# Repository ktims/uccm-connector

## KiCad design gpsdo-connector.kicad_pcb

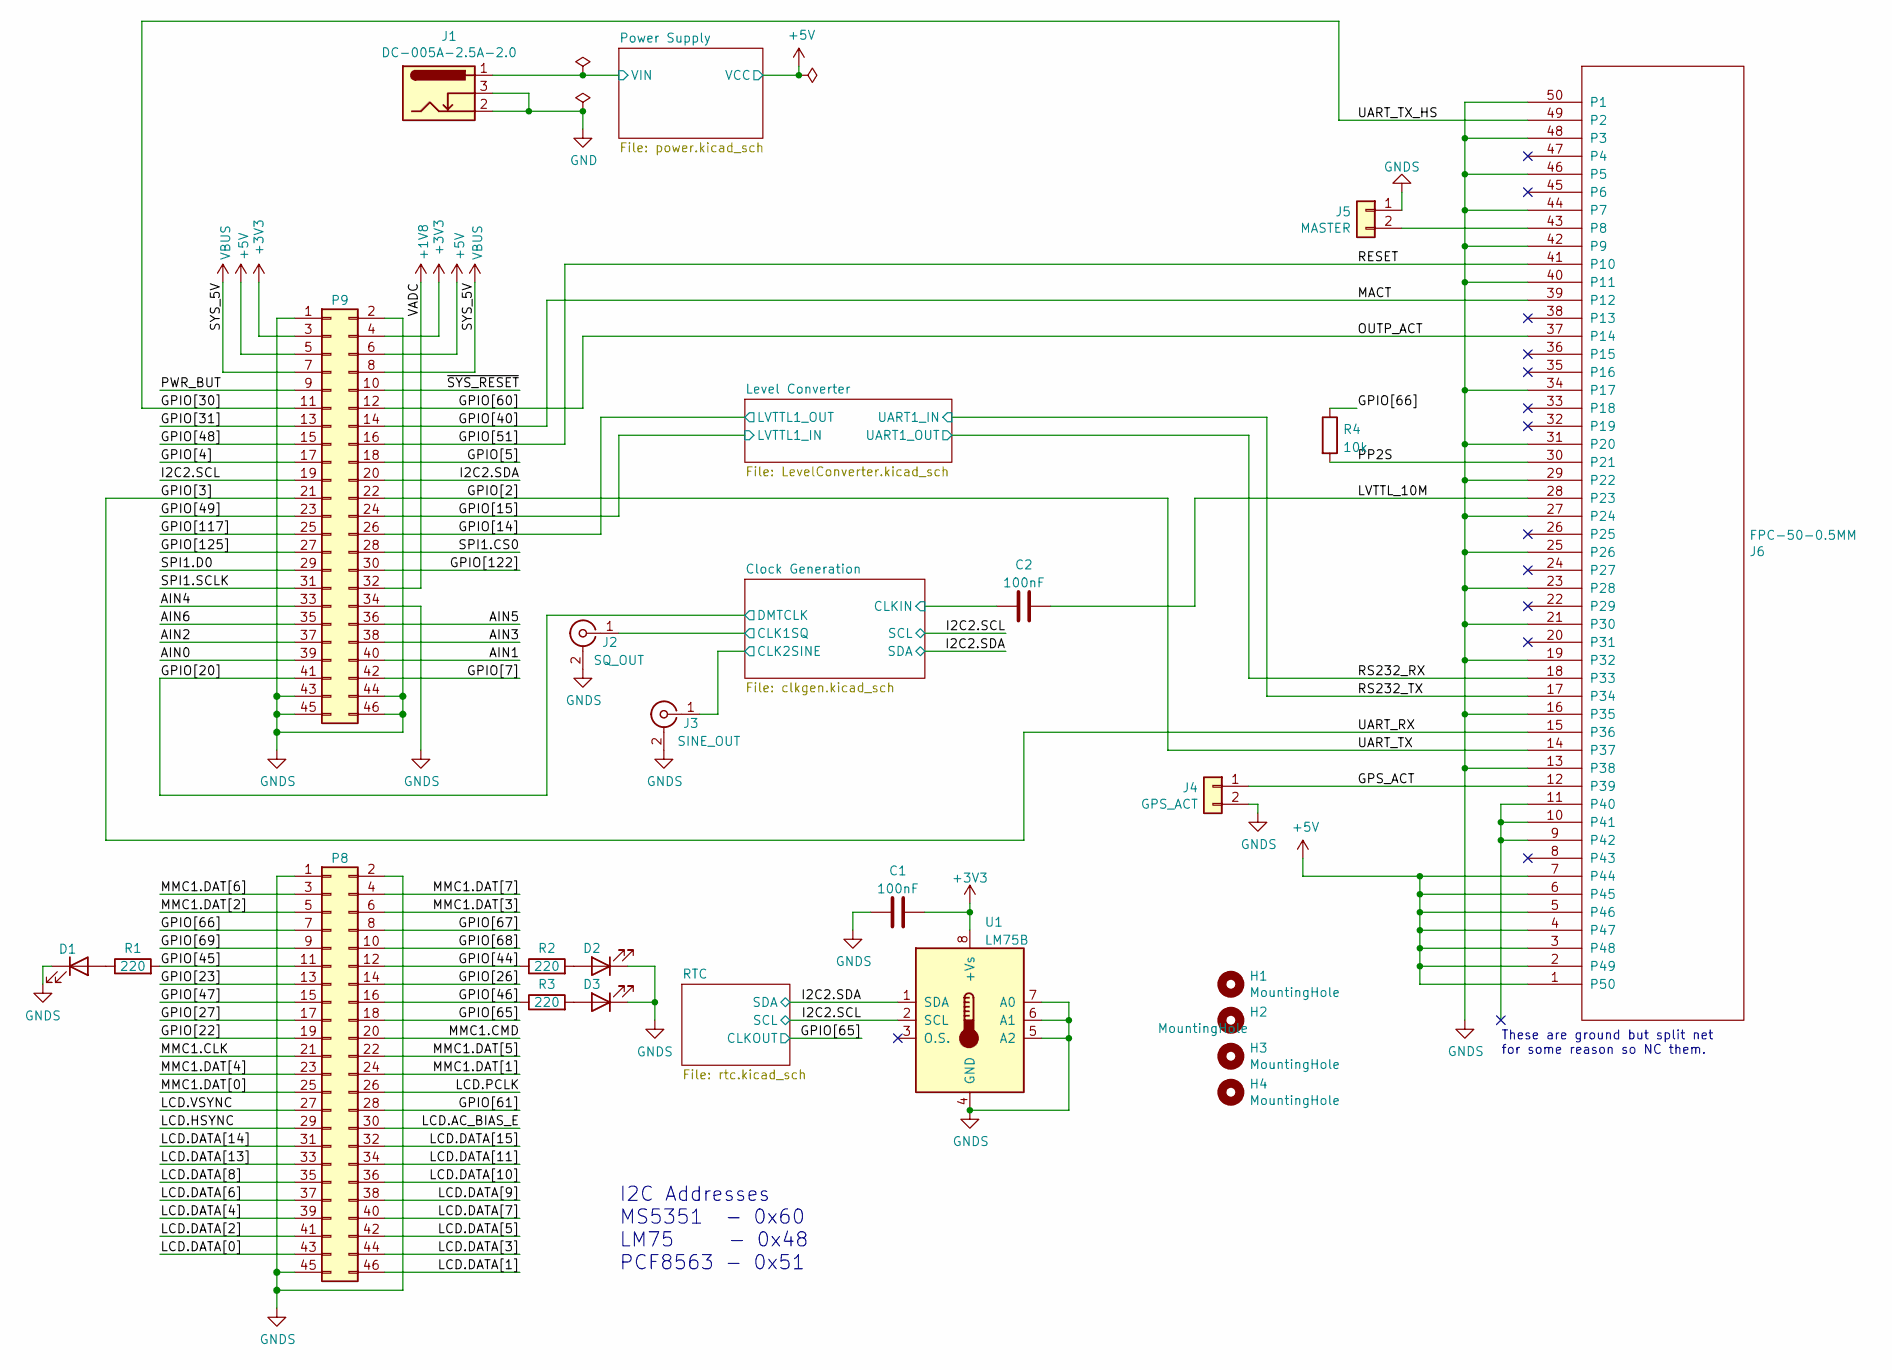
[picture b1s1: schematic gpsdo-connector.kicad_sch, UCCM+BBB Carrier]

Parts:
C1, C2: 100nF; C_0805_2012Metric_Pad1.18x1.45mm_HandSolder; LCSC C49678
D1, D2: LED; LED_0805_2012Metric_Pad1.15x1.40mm_HandSolder; LCSC C2297
D3: LED; LED_0805_2012Metric_Pad1.15x1.40mm_HandSolder; LCSC C84256
H1, H2, H3, H4: MountingHole; MountingHole_3.2mm_M3_DIN965
J1: DC-005A-2.5A-2.0; MPN DC-005A-2.5A-2.0; LCSC C480363
J2: SQ_OUT; DOSIN-801-0080; MPN DOSIN-801-0080; LCSC C521219
J3: SINE_OUT; DOSIN-801-0080; MPN DOSIN-801-0080; LCSC C521219
J4: GPS_ACT; PinHeader_1x02_P2.54mm_Vertical
J5: MASTER; PinHeader_1x02_P2.54mm_Vertical
J6: FPC-50-0.5MM; Hirose_FH12-50S-0.5SH_1x50-1MP_P0.50mm_Horizontal; MPN FH12-50S-0.5SH(55); LCSC C202116
P8, P9: BeagleBone_Black_Header; PinHeader_2x23_P2.54mm_Vertical
R1, R2, R3: 220; R_0805_2012Metric_Pad1.20x1.40mm_HandSolder; LCSC C17557
R4: 10k; R_0805_2012Metric_Pad1.20x1.40mm_HandSolder; LCSC C17414
U1: LM75B; MSOP-8_3x3mm_P0.65mm; LCSC C2837470

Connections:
+1V8: P9.32
+3V3: C1.2, P9.3, P9.4, U1.8 (+Vs); also elsewhere on the board
+5V: J6.1 (P50), J6.2 (P49), J6.3 (P48), J6.4 (P47), J6.5 (P46), J6.6 (P45), J6.7 (P44), P9.5, P9.6; also elsewhere on the board
/AIN0: P9.39
/AIN1: P9.40
/AIN2: P9.37
/AIN3: P9.38
/AIN4: P9.33
/AIN5: P9.36
/AIN6: P9.35
/Clock Generation/CLK1SQ: J2.1 (In); also elsewhere on the board
/Clock Generation/CLK2SINE: J3.1 (In); also elsewhere on the board
/Clock Generation/CLKIN: C2.1; also elsewhere on the board
/GPIO[2]: J6.14 (P37), P9.22
/GPIO[3]: J6.15 (P36), P9.21
/GPIO[4]: P9.17
/GPIO[5]: P9.18
/GPIO[7]: P9.42
/GPIO[14]: P9.26; also elsewhere on the board
/GPIO[15]: P9.24; also elsewhere on the board
/GPIO[20]: P9.41; also elsewhere on the board
/GPIO[22]: P8.19
/GPIO[23]: P8.13
/GPIO[26]: P8.14
/GPIO[27]: P8.17
/GPIO[30]: J6.49 (P2), P9.11
/GPIO[31]: P9.13
/GPIO[40]: J6.39 (P12), P9.14
/GPIO[44]: P8.12, R2.1
/GPIO[45]: P8.11, R1.2
/GPIO[46]: P8.16, R3.1
/GPIO[47]: P8.15
/GPIO[48]: P9.15
/GPIO[49]: P9.23
/GPIO[51]: J6.41 (P10), P9.16
/GPIO[60]: J6.37 (P14), P9.12
/GPIO[61]: P8.28
/GPIO[65]: P8.18; also elsewhere on the board
/GPIO[66]: P8.7, R4.1
/GPIO[67]: P8.8
/GPIO[68]: P8.10
/GPIO[69]: P8.9
/GPIO[117]: P9.25
/GPIO[122]: P9.30
/GPIO[125]: P9.27
/GPS_ACT: J4.1, J6.12 (P39)
/I2C2.SCL: P9.19, U1.2 (SCL); also elsewhere on the board
/I2C2.SDA: P9.20, U1.1 (SDA); also elsewhere on the board
/LCD.AC_BIAS_E: P8.30
/LCD.DATA[0]: P8.43
/LCD.DATA[1]: P8.46
/LCD.DATA[2]: P8.41
/LCD.DATA[3]: P8.44
/LCD.DATA[4]: P8.39
/LCD.DATA[5]: P8.42
/LCD.DATA[6]: P8.37
/LCD.DATA[7]: P8.40
/LCD.DATA[8]: P8.35
/LCD.DATA[9]: P8.38
/LCD.DATA[10]: P8.36
/LCD.DATA[11]: P8.34
/LCD.DATA[13]: P8.33
/LCD.DATA[14]: P8.31
/LCD.DATA[15]: P8.32
/LCD.HSYNC: P8.29
/LCD.PCLK: P8.26
/LCD.VSYNC: P8.27
/LVTTL_10M: C2.2, J6.28 (P23)
/MMC1.CLK: P8.21
/MMC1.CMD: P8.20
/MMC1.DAT[0]: P8.25
/MMC1.DAT[1]: P8.24
/MMC1.DAT[2]: P8.5
/MMC1.DAT[3]: P8.6
/MMC1.DAT[4]: P8.23
/MMC1.DAT[5]: P8.22
/MMC1.DAT[6]: P8.3
/MMC1.DAT[7]: P8.4
/PP2S: J6.30 (P21), R4.2
/PWR_BUT: P9.9
/Power Supply/VIN: J1.1; also elsewhere on the board
/RS232_RX: J6.18 (P33); also elsewhere on the board
/RS232_TX: J6.17 (P34); also elsewhere on the board
/SPI1.CS0: P9.28
/SPI1.D0: P9.29
/SPI1.SCLK: P9.31
/~SYS_RESET: P9.10
GND: J1.2, J1.3; also elsewhere on the board
GNDS: C1.1, D1.1 (K), D2.1 (K), D3.1 (K), J2.2 (Ext), J3.2 (Ext), J4.2, J5.1, J6.13 (P38), J6.16 (P35), J6.19 (P32), J6.21 (P30), J6.23 (P28), J6.25 (P26), J6.27 (P24), J6.29 (P22), J6.31 (P20), J6.34 (P17), J6.40 (P11), J6.42 (P9), J6.44 (P7), J6.46 (P5), J6.48 (P3), J6.50 (P1), P8.1, P8.2, P8.45, P9.1, P9.2, P9.34, P9.43, P9.44, P9.45, P9.46, U1.4 (GND), U1.5 (A2), U1.6 (A1), U1.7 (A0); also elsewhere on the board
unnamed: D1.2 (A), R1.1
unnamed: D2.2 (A), R2.2
unnamed: D3.2 (A), R3.2
unnamed: J5.2, J6.43 (P8)
VBUS: P9.7, P9.8

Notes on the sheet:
I2C Addresses MS5351 - 0x60 LM75 - 0x48 PCF8563 - 0x51
These are ground but split net for some reason so NC them.

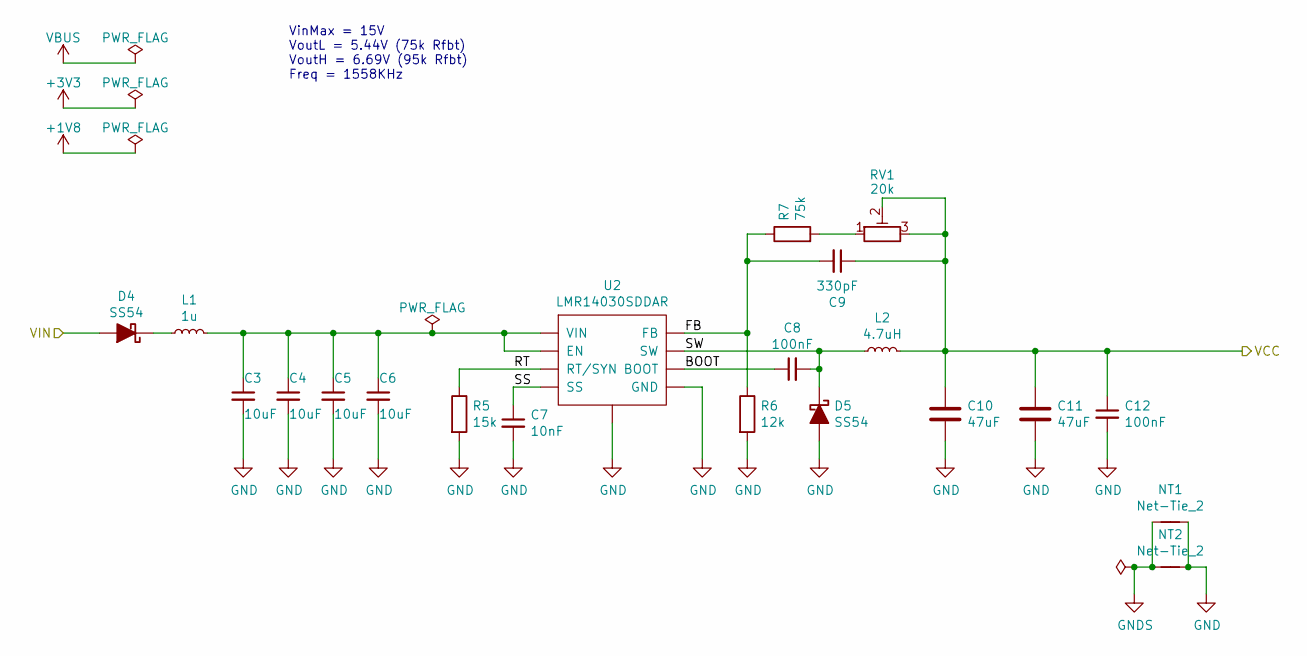
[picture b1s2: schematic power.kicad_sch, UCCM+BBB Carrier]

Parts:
C3, C4, C5, C6: 10uF; C_1206_3216Metric_Pad1.33x1.80mm_HandSolder; LCSC C1848
C7: 10nF; C_0805_2012Metric_Pad1.18x1.45mm_HandSolder; LCSC C1710
C8, C12: 100nF; C_0805_2012Metric_Pad1.18x1.45mm_HandSolder; LCSC C49678
C9: 330pF; C_0805_2012Metric_Pad1.18x1.45mm_HandSolder; LCSC C51207
C10, C11: 47uF; C_1206_3216Metric_Pad1.33x1.80mm_HandSolder; LCSC C96123
D4, D5: SS54; D_SMA; LCSC C22452
L1: 1u; L_1206_3216Metric_Pad1.22x1.90mm_HandSolder
L2: 4.7uH; L_Abracon_ASPI-0630LR; MPN MCS0630-4R7MN2; LCSC C385253
NT1, NT2: Net-Tie_2; NetTie-2_SMD_Pad2.0mm
R5: 15k; R_0805_2012Metric_Pad1.20x1.40mm_HandSolder; LCSC C17475
R6: 12k; R_0805_2012Metric_Pad1.20x1.40mm_HandSolder; LCSC C17444
R7: 75k; R_0805_2012Metric_Pad1.20x1.40mm_HandSolder; LCSC C17819
RV1: 20k; Trimpot_Bourns_3313J-1; MPN 3313J-1-203E; LCSC C124621
U2: LMR14030SDDAR; TI_SO-PowerPAD-8; LCSC C182078

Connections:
+5V: C9.1, C10.1, C11.1, C12.1, L2.2, RV1.2, RV1.3; also elsewhere on the board
/Power Supply/BOOT: C8.1, U2.1 (BOOT)
/Power Supply/FB: C9.2, R6.1, R7.1, U2.5 (FB)
/Power Supply/RT: R5.1, U2.4 (RT/SYN)
/Power Supply/SS: C7.1, U2.6 (SS)
/Power Supply/SW: C8.2, D5.1 (K), L2.1, U2.8 (SW)
/Power Supply/VIN: D4.2 (A); also elsewhere on the board
GND: C3.2, C4.2, C5.2, C6.2, C7.2, C10.2, C11.2, C12.2, D5.2 (A), NT1.2, NT2.2, R5.2, R6.2, U2.7 (GND), U2.9; also elsewhere on the board
GNDS: NT1.1, NT2.1; also elsewhere on the board
unnamed: C3.1, C4.1, C5.1, C6.1, L1.2, U2.2 (VIN), U2.3 (EN)
unnamed: D4.1 (K), L1.1
unnamed: R7.2, RV1.1

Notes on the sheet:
VinMax = 15V VoutL = 5.44V (75k Rfbt) VoutH = 6.69V (95k Rfbt) Freq = 1558KHz

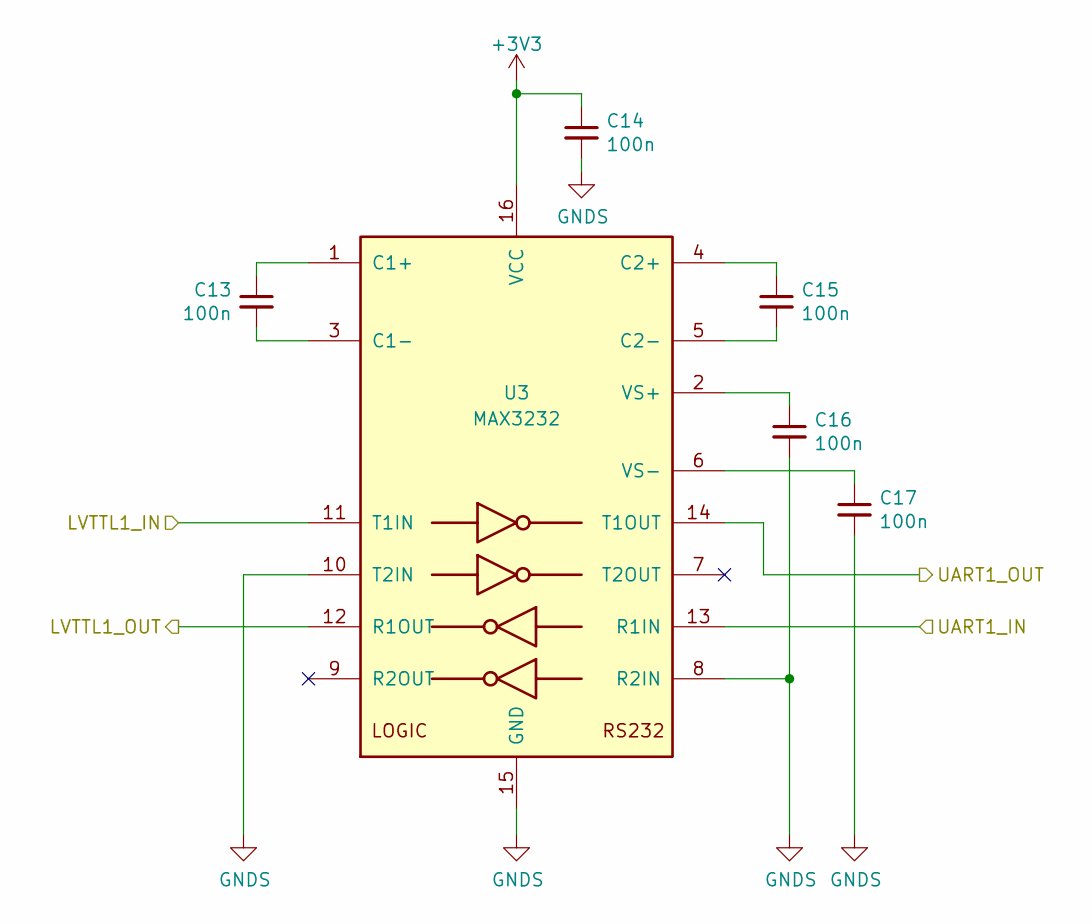
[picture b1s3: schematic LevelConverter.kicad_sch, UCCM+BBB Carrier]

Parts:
C13, C14, C15, C16, C17: 100n; C_0805_2012Metric_Pad1.18x1.45mm_HandSolder; LCSC C49678
U3: MAX3232; TSSOP-16_4.4x5mm_P0.65mm; MPN SP3232EEY-L/TR; LCSC C13482

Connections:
+3V3: C14.1, U3.16 (VCC); also elsewhere on the board
/GPIO[14]: U3.12 (R1OUT); also elsewhere on the board
/GPIO[15]: U3.11 (T1IN); also elsewhere on the board
/RS232_RX: U3.14 (T1OUT); also elsewhere on the board
/RS232_TX: U3.13 (R1IN); also elsewhere on the board
GNDS: C14.2, C16.2, C17.2, U3.8 (R2IN), U3.10 (T2IN), U3.15 (GND); also elsewhere on the board
unnamed: C13.1, U3.1 (C1+)
unnamed: C13.2, U3.3 (C1-)
unnamed: C15.1, U3.4 (C2+)
unnamed: C15.2, U3.5 (C2-)
unnamed: C16.1, U3.2 (VS+)
unnamed: C17.1, U3.6 (VS-)

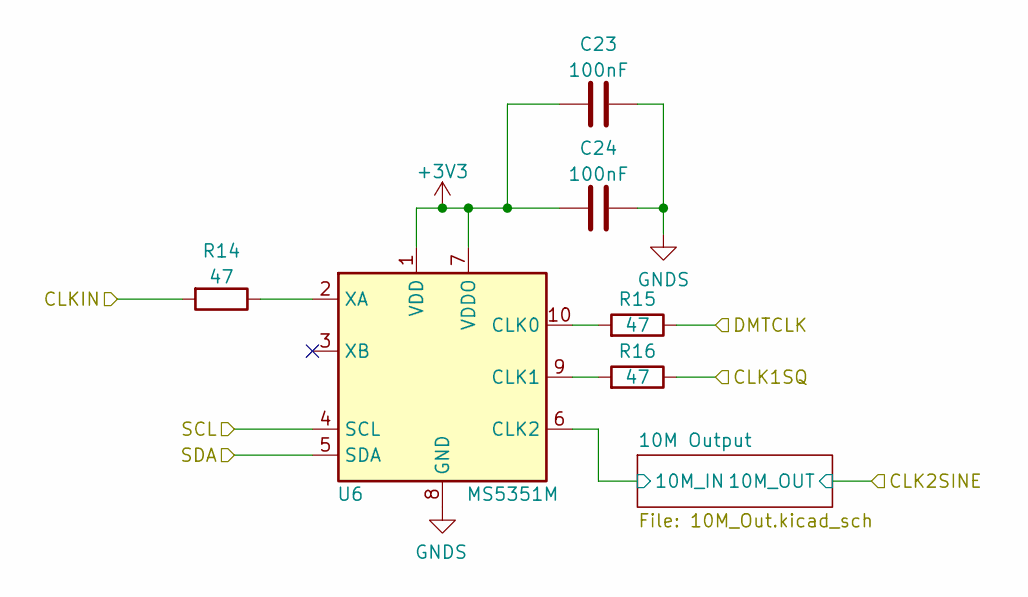
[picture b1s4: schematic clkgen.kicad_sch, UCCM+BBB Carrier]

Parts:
C23, C24: 100nF; C_0805_2012Metric_Pad1.18x1.45mm_HandSolder; LCSC C49678
R14, R15, R16: 47; R_0805_2012Metric_Pad1.20x1.40mm_HandSolder; LCSC C17714
U6: MS5351M; MSOP-10_3x3mm_P0.5mm; LCSC C1509083

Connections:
+3V3: C23.2, C24.2, U6.1 (VDD), U6.7 (VDDO); also elsewhere on the board
/Clock Generation/10M Filter/10M_IN: U6.6 (CLK2); also elsewhere on the board
/Clock Generation/CLK1SQ: R16.1; also elsewhere on the board
/Clock Generation/CLKIN: R14.2; also elsewhere on the board
/GPIO[20]: R15.1; also elsewhere on the board
/I2C2.SCL: U6.4 (SCL); also elsewhere on the board
/I2C2.SDA: U6.5 (SDA); also elsewhere on the board
GNDS: C23.1, C24.1, U6.8 (GND); also elsewhere on the board
unnamed: R14.1, U6.2 (XA)
unnamed: R15.2, U6.10 (CLK0)
unnamed: R16.2, U6.9 (CLK1)

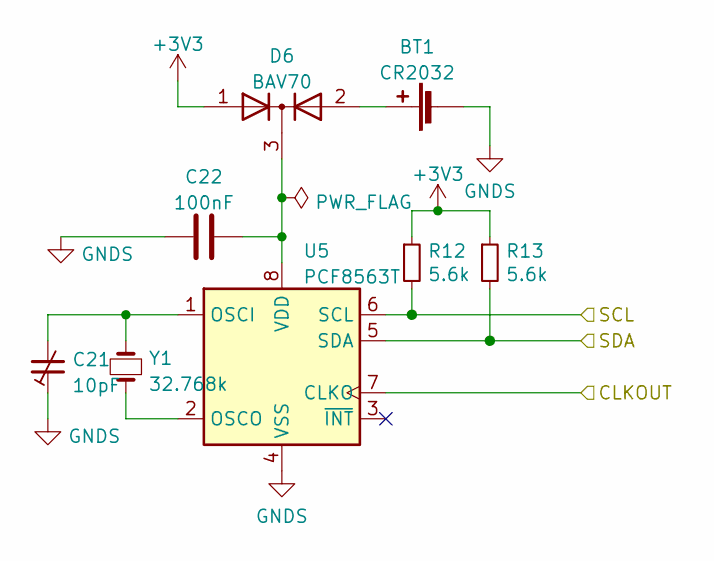
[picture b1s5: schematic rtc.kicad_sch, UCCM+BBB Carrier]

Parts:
BT1: CR2032; CR2032-BS-6-1; MPN BH-49B-5
C21: 10pF; C_0805_2012Metric_Pad1.18x1.45mm_HandSolder; LCSC C1785
C22: 100nF; C_0805_2012Metric_Pad1.18x1.45mm_HandSolder; LCSC C49678
D6: BAV70; SOT-23; LCSC C68978
R12, R13: 5.6k; R_0805_2012Metric_Pad1.20x1.40mm_HandSolder; LCSC C4382
U5: PCF8563T; SOIC-8_3.9x4.9mm_P1.27mm; MPN PCF8563T/5,518; LCSC C7440
Y1: 32.768k; Crystal_SMD_3215-2Pin_3.2x1.5mm; LCSC C32346

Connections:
+3V3: D6.1 (A), R12.1, R13.1; also elsewhere on the board
/GPIO[65]: U5.7 (CLKO); also elsewhere on the board
/I2C2.SCL: R12.2, U5.6 (SCL); also elsewhere on the board
/I2C2.SDA: R13.2, U5.5 (SDA); also elsewhere on the board
GNDS: BT1.2 (-), C21.1, C22.1, U5.4 (VSS); also elsewhere on the board
unnamed: BT1.1 (+), D6.2 (A)
unnamed: C21.2, U5.1 (OSCI), Y1.2
unnamed: C22.2, D6.3 (K), U5.8 (VDD)
unnamed: U5.2 (OSCO), Y1.1

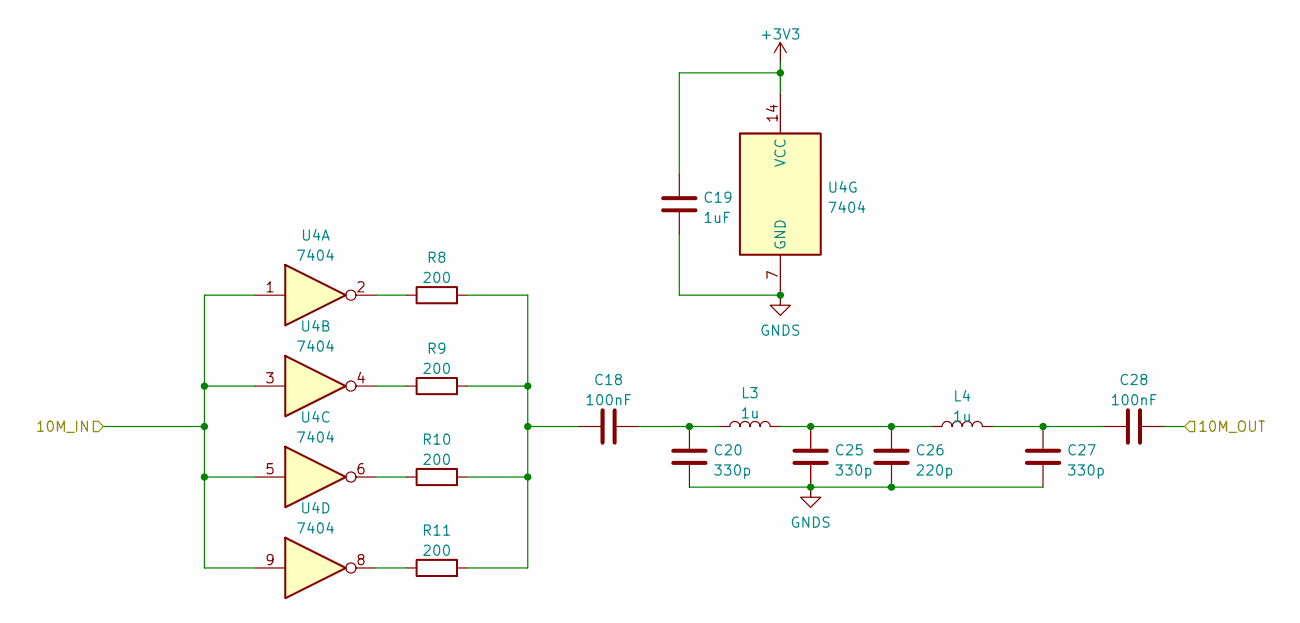
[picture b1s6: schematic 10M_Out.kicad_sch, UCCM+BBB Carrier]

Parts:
C18, C28: 100nF; C_0805_2012Metric_Pad1.18x1.45mm_HandSolder; LCSC C49678
C19: 1uF; C_0805_2012Metric_Pad1.18x1.45mm_HandSolder; LCSC C28323
C20, C25, C27: 330p; C_0603_1608Metric_Pad1.08x0.95mm_HandSolder; LCSC C1664
C26: 220p; C_0603_1608Metric_Pad1.08x0.95mm_HandSolder; LCSC C1603
L3, L4: 1u; L_0805_2012Metric_Pad1.15x1.40mm_HandSolder; LCSC C1042
R8, R9, R10, R11: 200; R_0805_2012Metric_Pad1.20x1.40mm_HandSolder; LCSC C17540
U4: 7404; SOIC-14_3.9x8.7mm_P1.27mm; LCSC C5590

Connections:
+3V3: C19.1, U4.14 (VCC); also elsewhere on the board
/Clock Generation/10M Filter/10M_IN: U4.1, U4.3, U4.5, U4.9; also elsewhere on the board
/Clock Generation/CLK2SINE: C28.1; also elsewhere on the board
GNDS: C19.2, C20.2, C25.2, C26.2, C27.2, U4.7 (GND); also elsewhere on the board
unnamed: C18.2, R8.2, R9.2, R10.2, R11.2
unnamed: C18.1, C20.1, L3.1
unnamed: C27.1, C28.2, L4.2
unnamed: C25.1, C26.1, L3.2, L4.1
unnamed: R8.1, U4.2
unnamed: R9.1, U4.4
unnamed: R10.1, U4.6
unnamed: R11.1, U4.8

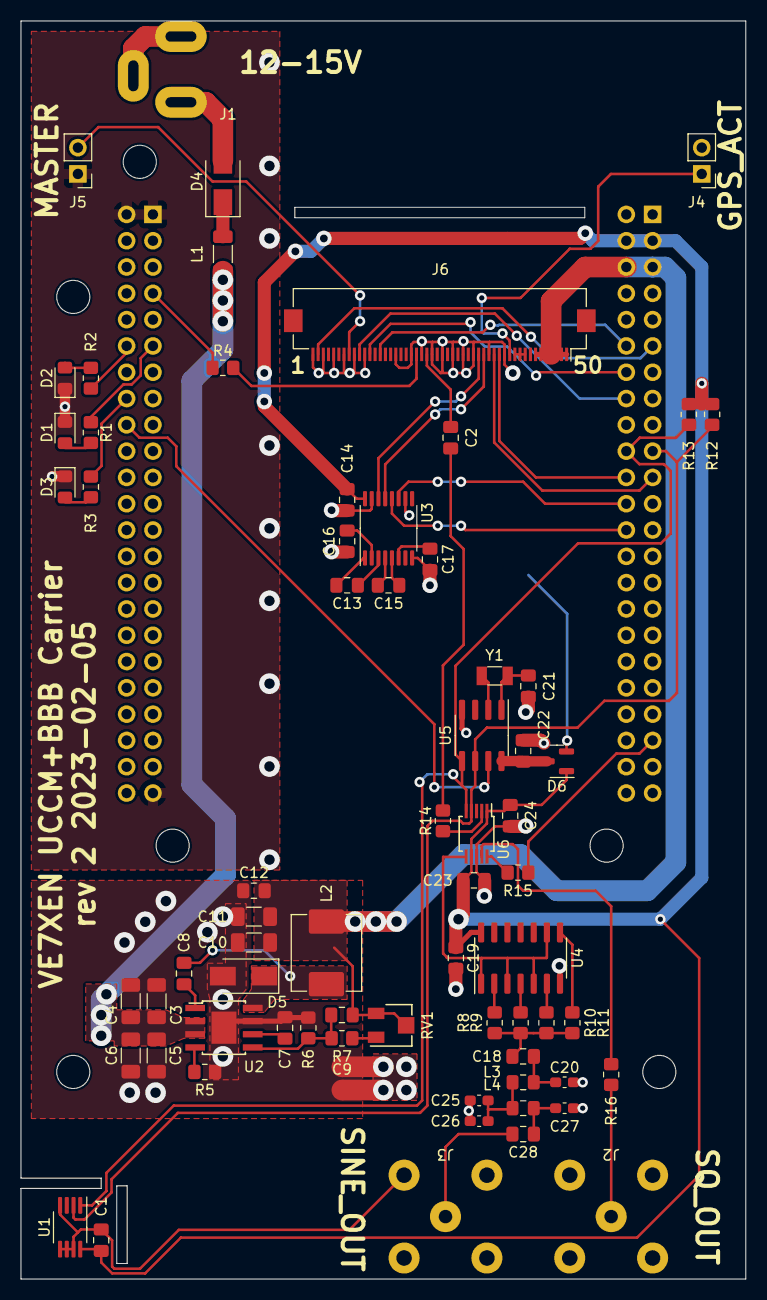
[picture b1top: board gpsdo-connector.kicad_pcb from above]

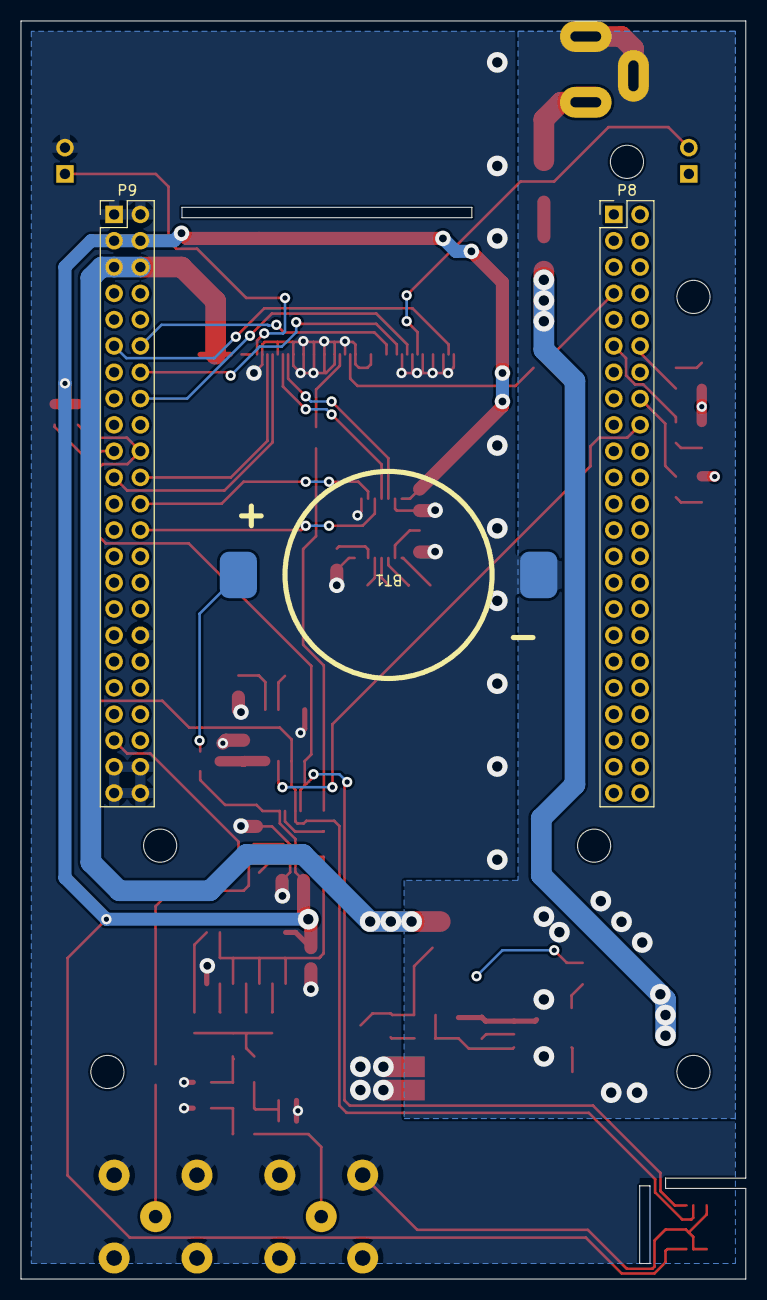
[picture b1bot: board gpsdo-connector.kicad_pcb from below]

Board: 2 copper layers, 70.0 x 121.5 mm, 79 parts (6 on the bottom side), 64 nets.

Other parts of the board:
MH2, MH3, MH4: MountingHole_3.2mm_M3_DIN965

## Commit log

2022-10-08 VE7XEN BBB Carrier rev 1
2022-10-08 rev 1 DFM fixes, kibot automation
2022-10-08 Fix github actions
2022-10-08 Fix footprint of C19 JLCPCB DFM identified 0805 part fitted on 1206 footprint
2023-02-06 Fix 10M output filter
